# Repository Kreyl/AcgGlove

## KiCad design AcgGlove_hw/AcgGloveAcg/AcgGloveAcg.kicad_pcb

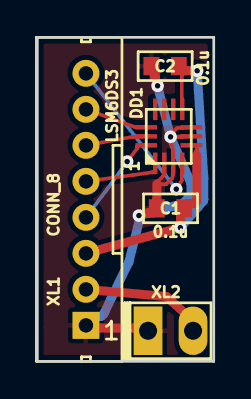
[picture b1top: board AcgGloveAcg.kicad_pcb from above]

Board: 2 copper layers, 9.8 x 18.0 mm, 5 parts (0 on the bottom side), 8 nets.

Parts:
C1, C2: 0.1u; CAP_0603
DD1: LSM6DS3; 14_3x2d5_p0d5
XL1: CONN_8; WB-08(MW-8M)
XL2: CONN_2; SLD_2_2D5

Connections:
/ACG_CS: DD1.12, XL1.7
/ACG_INT1: DD1.4, XL1.8
/ACG_MISO: DD1.1, XL1.5
/ACG_MOSI: DD1.14, XL1.4
/ACG_PWR: C1.1, C2.1, DD1.5, DD1.8, XL1.3
/ACG_SCK: DD1.13, XL1.6
/VibroOut: XL1.2, XL2.2
GND: C1.2, C2.2, DD1.2, DD1.3, DD1.6, DD1.7, XL1.1, XL2.1

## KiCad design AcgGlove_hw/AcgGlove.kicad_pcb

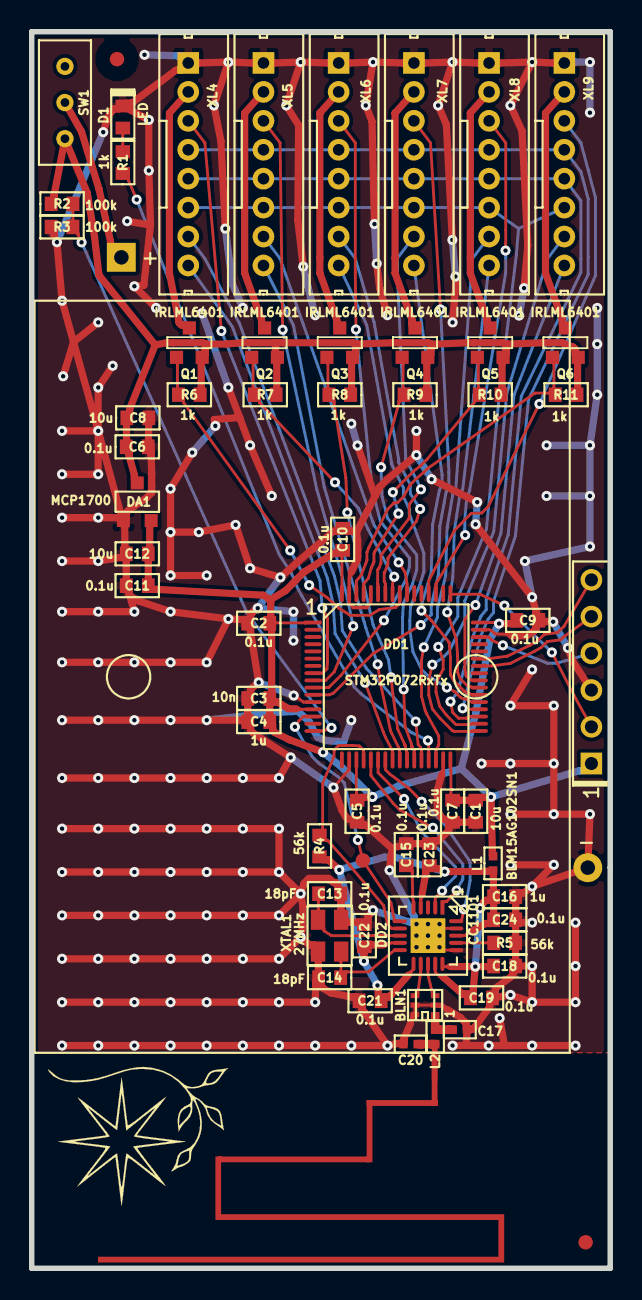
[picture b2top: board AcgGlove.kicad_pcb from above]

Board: 2 copper layers, 40.0 x 85.5 mm, 63 parts (0 on the bottom side), 58 nets.

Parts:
ANT1: ANT_PCB_MONO; ANT_868_ARMLETG
B1: BAT; BATTERY_AAA_X3
BLN1: BALUN868JOHANSON; BALUN_JOHANSON868
C1, C8, C12: 10u; CAP_0603
C2, C5, C6, C7, C9, C10, C11, C15, C18, C19, C21, C22, C23, C24: 0.1u; CAP_0603
C3: 10n; CAP_0603
C4, C16: 1u; CAP_0603
C13, C14: 18pF; CAP_0603
C17, C20: *; CAP_0402
D1: LED; LED_0603
DA1: MCP1700; SOT23-3A
DD1: STM32F072RxTx; LQFP64
DD2: CC1101; QFN20
L1: BLM15AG102SN1; IND_0402
L2: *; IND_0402
Logo1: Logo; Ostranna_12d7_10d1
Q1, Q2, Q3, Q4, Q5, Q6: IRLML6401; SOT23-3
R1, R6, R7, R8, R9, R10, R11: 1k; RES_0603
R2, R3: 100k; RES_0603
R4, R5: 56k; RES_0603
RP1, RP2: REFPOINT; REF_POINT_1MM
SW1: SS-9; SW_SS-1P2T
TP1: TESTPOINT; TESTPOINT_1MM
XL1: CONN_6; PLS-6
XL4, XL5, XL6, XL7, XL8, XL9: CONN_8; WB-08(MW-8M)
XTAL1: 27MHz; 03225C4

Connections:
+3.3V: C1.2, C2.1, C3.1, C4.1, C5.1, C7.1, C9.1, C10.1, C11.1, C12.1, DA1.2, DD1.1, DD1.13, DD1.19, DD1.32, DD1.48, DD1.64, L1.2, XL1.1
+BATT: C6.1, C8.1, DA1.3, Q1.2, Q2.2, Q3.2, Q4.2, Q5.2, Q6.2, R2.1, R6.1, R7.1, R8.1, R9.1, R10.1, R11.1, SW1.1
/ACG_CS1: DD1.28, XL4.7
/ACG_CS2: DD1.55, XL5.7
/ACG_CS3: DD1.58, XL6.7
/ACG_CS4: DD1.59, XL7.7
/ACG_CS5: DD1.30, XL8.7
/ACG_CS6: DD1.33, XL9.7
/ACG_INT1: DD1.24, XL4.8
/ACG_INT2: DD1.25, XL5.8
/ACG_INT3: DD1.37, XL6.8
/ACG_INT4: DD1.38, XL7.8
/ACG_INT5: DD1.39, XL8.8
/ACG_INT6: DD1.40, XL9.8
/ACG_MISO: DD1.35, XL4.5, XL5.5, XL6.5, XL7.5, XL8.5, XL9.5
/ACG_MOSI: DD1.36, XL4.4, XL5.4, XL6.4, XL7.4, XL8.4, XL9.4
/ACG_PWR1: DD1.8, XL4.3
/ACG_PWR2: DD1.9, XL5.3
/ACG_PWR3: DD1.10, XL6.3
/ACG_PWR4: DD1.11, XL7.3
/ACG_PWR5: DD1.51, XL8.3
/ACG_PWR6: DD1.52, XL9.3
/ACG_SCK: DD1.34, XL4.6, XL5.6, XL6.6, XL7.6, XL8.6, XL9.6
/ADC_BATTERY: DD1.16, R2.2, R3.1
/ANT1: BLN1.1, C17.1, L2.2
/ANT2: ANT1.1, C20.1, L2.1
/BAT_IN: B1.A, SW1.2
/CC_CS: DD1.20, DD2.7, R4.1
/CC_GDO0: DD1.14, DD2.6, TP1.1
/CC_MISO: DD1.22, DD2.2
/CC_MOSI: DD1.23, DD2.20
/CC_SCK: DD1.21, DD2.1
/RF1: BLN1.4, DD2.12
/RF2: BLN1.3, DD2.13
/SWCLK: DD1.49, XL1.2
/SWDIO: DD1.46, XL1.4
/UART_RX: DD1.43, XL1.6
/UART_TX: DD1.42, XL1.5
/VIBRO_CTRL1: DD1.56, Q1.1, R6.2
/VIBRO_CTRL2: DD1.57, Q2.1, R7.2
/VIBRO_CTRL3: DD1.26, Q3.1, R8.2
/VIBRO_CTRL4: DD1.27, Q4.1, R9.2
/VIBRO_CTRL5: DD1.61, Q5.1, R10.2
/VIBRO_CTRL6: DD1.62, Q6.1, R11.2
/VibroOut1: Q1.3, XL4.2
/VibroOut2: Q2.3, XL5.2
/VibroOut3: Q3.3, XL6.2
/VibroOut4: Q4.3, XL7.2
/VibroOut5: Q5.3, XL8.2
/VibroOut6: Q6.3, XL9.2
GND: B1.C, BLN1.2, BLN1.5, BLN1.6, C1.1, C2.2, C3.2, C4.2, C5.2, C6.2, C7.2, C8.2, C9.2, C10.2, C11.2, C12.2, C13.2, C14.2, C15.1, C16.2, C17.2, C18.2, C19.2, C20.2, C21.2, C22.2, C23.2, C24.2, D1.C, DA1.1, DD1.12, DD1.18, DD1.31, DD1.47, DD1.60, DD1.63, DD2.16, DD2.19, DD2.PAD, R3.2, R5.2, XL1.3, XL4.1, XL5.1, XL6.1, XL7.1, XL8.1, XL9.1, XTAL1.H
unnamed: C13.1, DD2.8, XTAL1.1
unnamed: C14.1, DD2.10, XTAL1.2
unnamed: C15.2, DD2.5
unnamed: D1.A, R1.2
unnamed: DD1.29, R1.1
unnamed: DD2.17, R5.1
VCC: C16.1, C18.1, C19.1, C21.1, C22.1, C23.1, C24.1, DD2.4, DD2.9, DD2.11, DD2.14, DD2.15, DD2.18, L1.1, R4.2

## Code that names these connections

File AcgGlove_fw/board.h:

/*
 * board.h
 *
 *  Created on: 01.02.2017
 *      Author: Kreyl
 */

#pragma once

#include <inttypes.h>

// ==== General ====
#define BOARD_NAME          "AcgGlove1"
#define APP_NAME            "AcgGlove"

// MCU type as defined in the ST header.
#define STM32F072xB     // no matter, 8 or B

// Freq of external crystal if any. Leave it here even if not used.
#define CRYSTAL_FREQ_HZ         12000000

#define SYS_TIM_CLK             (Clk.APBFreqHz)

#define SIMPLESENSORS_ENABLED   FALSE
#define BUTTONS_ENABLED         FALSE
#define ADC_REQUIRED            FALSE
#define I2C1_ENABLED            FALSE
#define I2C_USE_SEMAPHORE       FALSE

#if 1 // ========================== GPIO =======================================
// PortMinTim_t: GPIO, Pin, Tim, TimChnl, invInverted, omPushPull, TopValue

// Battery measurement
#define BAT_MEAS_PIN    GPIOA, 0

#define LED_PIN         GPIOB, 10, omPushPull

#define INDIVIDUAL_EXTI_IRQ_REQUIRED    TRUE

// Acg
#define ACG_SPI         SPI2
#define ACG_SCK_PIN     GPIOB, 13, omPushPull, pudNone, AF0
#define ACG_MISO_PIN    GPIOB, 14, omPushPull, pudNone, AF0
#define ACG_MOSI_PIN    GPIOB, 15, omPushPull, pudNone, AF0

#define ACG_INT1        GPIOC, 4
#define ACG_CS1         GPIOB, 2
#define ACG_PWR1        GPIOC, 0

#define ACG_INT2        GPIOC, 5
#define ACG_CS2         GPIOB, 3
#define ACG_PWR2        GPIOC, 1

#define ACG_INT3        GPIOC, 6
#define ACG_CS3         GPIOB, 6
#define ACG_PWR3        GPIOC, 2

#define ACG_INT4        GPIOC, 7
#define ACG_CS4         GPIOB, 7
#define ACG_PWR4        GPIOC, 3

#define ACG_INT5        GPIOC, 8
#define ACG_CS5         GPIOB, 11
#define ACG_PWR5        GPIOC, 10

#define ACG_INT6        GPIOC, 9
#define ACG_CS6         GPIOB, 12
#define ACG_PWR6        GPIOC, 11


// UART
#define UART_GPIO       GPIOA
#define UART_TX_PIN     9
#define UART_RX_PIN     10

// Radio: SPI, PGpio, Sck, Miso, Mosi, Cs, Gdo0
#define CC_Setup0       SPI1, GPIOA, 5,6,7, 4, 0

#endif // GPIO

#if 1 // ========================== USART ======================================
#define PRINTF_FLOAT_EN FALSE
#define CMD_UART        USART1
#define UART_USE_INDEPENDENT_CLK    TRUE
#define UART_TXBUF_SZ   1024

#endif

#if 1 // ========================== USB ========================================
#define USBDrv          USBD1   // USB driver to use

// CRS
#define CRS_PRESCALER   RCC_CRS_SYNC_DIV1
#define CRS_SOURCE      RCC_CRS_SYNC_SOURCE_USB
#define CRS_POLARITY    RCC_CRS_SYNC_POLARITY_RISING
#define CRS_RELOAD_VAL  ((48000000 / 1000) - 1) // Ftarget / Fsync - 1
#define CRS_ERROR_LIMIT 34
#define HSI48_CALIBRATN 32
#endif

#if ADC_REQUIRED // ======================= Inner ADC ==========================
#define ADC_MEAS_PERIOD_MS  450
// Clock divider: clock is generated from the APB2
#define ADC_CLK_DIVIDER     adcDiv2

// ADC channels
#define ADC_LUM_CHNL        1

#define ADC_VREFINT_CHNL    17  // All 4xx, F072 and L151 devices. Do not change.
#define ADC_CHANNELS        { ADC_LUM_CHNL, ADC_VREFINT_CHNL }
#define ADC_CHANNEL_CNT     2   // Do not use countof(AdcChannels) as preprocessor does not know what is countof => cannot check
#define ADC_SAMPLE_TIME     ast55d5Cycles
#define ADC_SAMPLE_CNT      8   // How many times to measure every channel

#define ADC_SEQ_LEN         (ADC_SAMPLE_CNT * ADC_CHANNEL_CNT)

#endif

#if 1 // =========================== DMA =======================================
#define STM32_DMA_REQUIRED  TRUE
// ==== Uart ====
#define UART_DMA_TX     STM32_DMA1_STREAM2
#define UART_DMA_RX     STM32_DMA1_STREAM3
#define UART_DMA_CHNL   0   // Dummy

// ==== I2C1 ====
#define I2C1_DMA_TX     STM32_DMA1_STREAM2
#define I2C1_DMA_RX     STM32_DMA1_STREAM3
#define I2C1_DMA_CHNL   0 // Dummy

// ==== ACG ====
#define ACG_DMA_TX       STM32_DMA1_STREAM5
#define ACG_DMA_RX       STM32_DMA1_STREAM4
#define ACG_DMA_CHNL     0 // Dummy

#if ADC_REQUIRED
#define ADC_DMA         STM32_DMA1_STREAM1
#define ADC_DMA_MODE    STM32_DMA_CR_CHSEL(0) |   /* dummy */ \
                        DMA_PRIORITY_LOW | \
                        STM32_DMA_CR_MSIZE_HWORD | \
                        STM32_DMA_CR_PSIZE_HWORD | \
                        STM32_DMA_CR_MINC |       /* Memory pointer increase */ \
                        STM32_DMA_CR_DIR_P2M |    /* Direction is peripheral to memory */ \
                        STM32_DMA_CR_TCIE         /* Enable Transmission Complete IRQ */
#endif // ADC

#endif // DMA

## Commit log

2017-12-27 Sch in progress
2017-12-28 Sent to factory
2018-05-08 + First fw commit
2018-05-09 6 acg init ok
2018-05-09 + Led ok + CC ok
2018-05-10 + Antenna matched
2018-05-10 + data flow from all 6 acg received in main thd
2018-05-11 + CC transmits long pkt
2018-05-11 Acg data seems to be transmitted
2019-02-03 + csv
2019-02-04 Switch to Atollic
